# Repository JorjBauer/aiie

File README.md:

# Aiie!

Aiie! is an Apple //e emulator, written ground-up for the Teensy 4.1 (originally for the Teensy 3.6).

The name comes from a game I used to play on the Apple //e back around 1986 - Ali Baba and the Forty Thieves, published by Quality Software in 1981.

[http://crpgaddict.blogspot.com/2013/07/game-103-ali-baba-and-forty-thieves-1981.html](http://crpgaddict.blogspot.com/2013/07/game-103-ali-baba-and-forty-thieves-1981.html)

When characters in the game did damage to each other, they exclaimed something like "HAH! JUST A SCRATCH!" or "AAARGH!" or "OH MA, I THINK ITS MY TIME" [sic]. One of these exclamations was "AIIYEEEEE!!"

## Desktop version

As of 2026, there's a full desktop build of Aiie - but it's not here. Take a look [https://whimology.com/aiie/](on whimology.com) for the full releases.

## Build log:

  [https://hackaday.io/project/19925-aiie-an-embedded-apple-e-emulator](https://hackaday.io/project/19925-aiie-an-embedded-apple-e-emulator)

# Getting the ROMs

As with many emulators, you have to go get the ROMs yourself. I've got the ROMs that I dumped out of my Apple //e. You can probably get yours a lot easier.

There are two files that you'll need:

* apple2e.rom  -- a 32k dump of the entire Apple //e ROM
* disk.rom     -- a 256 byte dump of the DiskII controller ROM (16-sector P5)

The MD5 sums of those files are:

* 003a780b461c96ae3e72861ed0f4d3d9 apple2e.rom
* 2020aa1413ff77fe29353f3ee72dc295 disk.rom
From those, the appropriate headers will be automatically generated by "make roms" (or any other target that relies on the ROMs).

The hard-disk card's ROM (hd32.rom), the mouse card's ROM (mouse.rom) and the parallel printer card's ROM (parallel.rom) are Aiie's own, written for the 65C02 in apple/hd32rom.s, apple/mouserom.s and apple/parallelrom.s. The assembled images are bundled, so nothing has to be downloaded or assembled to build. After changing a source, "make firmware" reassembles them; that needs ca65 and ld65 from the cc65 suite. The printer ROM keeps the Apple card's Control-I commands (I/M reset, K/O toggle the line feed, nH/nL and nJ/nN set the width and stop the screen echo, a control character becomes the new command character) and keeps Applesoft's cursor column in step with the printer so PRINT with commas, TAB( and HTAB line up on paper.

# Building (for the Teensy)

The directory 'teensy' contains 'teensy.ino' - the Arduino development environment project file. You'll need to open that up and compile from within.

However.

I built this on a Mac, and I used a lot of symlinks because of limitations in the Arduino IDE. There's no reason that shouldn't work under Linux, but I have absolutely no idea what Windows will make of it. I would expect trouble. No, I won't accept pull requests that remove the symlinks and replace them with the bare files. Sorry.

Also, you'll have to build the ROM headers (above) with 'make roms' before you can build the Teensy .ino file.

If anyone knows how to make the Arduino development environment do any form of scripting that could be used to generate those headers, I'd gladly adopt that instead of forcing folks to run the Perl script via Makefile. And if you have a better way of dealing with subfolders of code, with the Teensy-specific code segregated as it is, I'm all ears...

I compile this with optimization set to "Faster" for the Teensy 4.1 at 528MHz - I've been successful underclocking it to increase the battery life. YMMV, the Teensy 4.1 will run up to 600MHz.

## Environment and Libraries

I have built this with Arduino 1.8.13 and TeensyDuino 1.54b5 and Arduino 2.3.7 and Teensy 1.59.0.

      https://www.pjrc.com/teensy/td_download.html

These libraries I'm using right from Teensy's environment: TimerOne; SPI; EEPROM; Time; Keypad; SdFat (previously called "SdFat-beta" but renamed in TeensyDuino 1.54).

You'll also need the ILI9341_t3n library from

       https://github.com/KurtE/ILI9341_t3n/

As of this writing, the master branch does not work for Aiie; but the branch "dma_new_fix" is fine. I'd recommend checking out that branch if it exists.

# Running (on the Teensy)

The reset/menu button (F10 on a keyboard) freezes the Apple //e and brings up the BIOS: one panel of settings in the style of the IIgs control panel. Up and Down pick a row, Left and Right change a value, Return opens a row that ends in "...", and Escape goes back (or, from the main list, resumes the //e).

## The main list

* **Resume**: return to the running Apple //e.
* **Reset the //e (warm)**: equivalent to pressing Ctrl-Reset on the real hardware. Hold both joystick buttons before selecting Reset to trigger the Apple //e self-test.
* **Reboot the //e (cold)**: reboot the emulated machine without ejecting disks.
* **Reboot and eject disks**: full power-cycle: ejects all disks and reboots.
* **Disk drive 1 / 2** and **Hard drive 1 / 2**: what is in each drive. Return opens a file browser; pick an image to insert it, or the "Eject" row at the top of the list to remove what is there. Type to narrow the list. Floppies: .dsk, .po, .nib and .woz (.nib images aren't heavily tested for write support). Hard drives: raw 32MB .img/.hdv files, or .2mg.
* **Cards...**, **Display...**, **Paddles...**, **Network...**: screens of their own, below.
* **Volume**: the speaker volume (0 to 15).
* **CPU speed**: Half (511.5 kHz), 1x (1.023 MHz), 2x (2.046 MHz) and 4x (4.092 MHz); the desktop build goes on to 8x, 16x, 128x and 256x.
* **Advanced...**: drop to the Apple //e monitor prompt (useful for debugging); the debug overlay, which cycles through off, FPS, memory free, paddles, PC, cycles, battery, time, disk and network; and the snapshot (see "Suspend and Restore" below). On the Teensy this is also where the firmware is updated from an AIIE.HEX on the SD card.
* **About Aiie**: version and build information.

## Cards

Assigns cards to slots 1 through 7, or 0 to remove a card. Type a digit to put the highlighted card in that slot directly, or step through the slots with Left and Right. If two cards conflict (same slot), the other card is moved to the lowest free slot. Slot 3 only suits the Uthernet, since the //e's own 80-column firmware lives there.

* **Disk II**: default slot 6.
* **Parallel printer**: default slot 1.
* **Hard disk**: default slot 7.
* **Mouse**: off by default; works in any slot but 3.
* **Mockingboard**: default slot 4.
* **Uthernet II**: off by default.
* **RamWorks**: the size of the auxiliary memory expansion, in megabytes, or "not installed".
* **Reset to defaults**: restores the default slot assignments.

Card changes are saved and persist across power cycles. A change cannot take effect in the running machine (the //e's boot scan has already run), so once you change a slot, Resume is disabled until you Reset or Reboot.

## Display

* **Display type**: cycles through four video modes: RGB, NTSC-like, B&W, and Mono.
* **Video7 color text**: whether the machine has an RGB card with the Video7 color-text extensions (see video7.md).
* **Luminance cutoff**: the brightness at which a B&W pixel is lit; Left/Right step it by one, - and + by sixteen.

### Display modes

"Display type" has four values, and they're only really implemented for text and hi-res modes (not for lo-res modes). To describe them, I have to talk about the details of the Apple II display system.

In hires modes, the Apple II can only display certain colors in certain horizontal pixel columns. Because of how the composite video out works, the color "carries over" from one pixel to its neighbor; multiple pixels turned on in a row makes them all white. Which means that, if you're trying to display a picture in hires mode, you get color artifacts on the edges of white areas.

The Apple Color Composite Monitor had a button on it that turned on "Monochrome" mode, with the finer resolution necessary to display the pixels without the color cast. So its two display modes would be the ones I call "NTSC-like" and "Black and White."

There are two other video modes. The "RGB" mode (the default, because it's my preference) shows the color pixels as they're actually drawn in to memory. That means there can't be a solid field of, for example, orange; there can only be vertical stripes of orange with black between them.

The last mode is "Monochrome" which looks like the original "Monitor II", a black-and-green display.

## Paddles

Flips either paddle axis, and plots the live paddle position in a target so you can check them.

## Network

The Uthernet II card's slot, the virtual subnet the NAT hands the Apple, and the inbound ports to forward to it. On the Teensy this is also where the WiFi name and password go, with a Connect row and a live link status; on the desktop the emulator rides the host's own connection, so there is nothing to join, and a port offset lets it open privileged ports without root.

The Teensy uses a ESP-01 for network access. The ESP-01 is limited to 4 active connections - that's a combination of inbound and outbound. If you set 3 different ports for inbound traffic (which are necessary because the Apple might be using raw sockets on the Uthernet, thus we have no way to tell the ESP-01 about its incoming traffic without this configuration) you only have 1 socket available for outbound traffic. If you set four listening ports, you won't be able to connect any outbound sessions at all.

There are a couple problems with the ESP-01 as-wired in the Aiie R9 PCB. I designed the PCB many years before actually wiring up the ESP-01 so it's not surprising that I didn't quite have it right. You'll need to add a 470uF and 0.1uF capacitor (10v) right at the ESP-01's power pins; and 10uF (10v) on the 3.3v regulator output. The device does not like the ESP-01 being turned on after you've booted the Aiie - it doesn't cause damage, but will reboot the machine.

I'm unlikely to build a R10 PCB unless I get specific requests for it. Networking support on an Apple //e emulator is *so* esoteric - nobody's been beating down my door asking for it. But I do have other thoughts of what I might do with the core work from this project, for a new hardware build in future...

## Suspend and Restore

The Teensy can be fully suspended and restored -- including what disks are inserted. It's a full VM hibernation. It currently writes to a file named "suspend.vm" in the root of the MicroSD card. (I would like to be able to select from multiple suspend/restore files eventually. It wouldn't be terribly hard; it's just that the BIOS interface is very limited.)

# Building (on a Mac)

This wasn't the initial purpose of this emulator, but I've built on to it as the first test target for most functionality over the past 9 years. The SDL build works with MacOS 10.11.6 and Homebrew or newer, and you can build and run it like this:

```
  $ make sdl
  $ ./aiie-sdl /path/to/disk.dsk
```

As the name implies, this requires that SDL is installed and in /usr/local/lib. I've done that with Homebrew like this

```
  $ brew install sdl2
```

When running, F10 enters the BIOS.

# Building (on Linux)

Years ago I experimented with Aiie running under a handmade OS on a Raspberry Pi Zero W; the hardware is decent, and cheap. I just don't want Linux in the way. So I built JOSS (see [my Hackaday page about JOSS](https://hackaday.io/project/19925-aiie-an-embedded-apple-e-emulator/log/87286-entry-18-pi-zero-w-and-joss)). 

Well, performance under JOSS is poor, so I built a Linux framebuffer wrapper for Aiie so that I can do performance testing on the Zero W, directly between JOSS and Linux. 

```
$ make linuxfb
$ ./linuxfb
```

There's no guarantee that this will still build; I don't have that environment any longer, and haven't tried to maintain it. I will probably purge it from the master branch in the future and it can live on in the git history.

# Building for the web or electron

You'll find a good number of #ifdefs related to EMSCRIPTEN in the code, but no WASM build here.

In 2026 I've needed a web build of this for a demonstration. Unrelated, I've been building a number of games in Electron for cross-platform support. It's not packaged here - it shares a framework with the games I've written - but the executables are [available on their own site](https://github.com/JorjBauer/aiie-electron-app/) if you want to run this as a standalone application. And stay tuned, I've got a web presence for an upcoming (fall 2026) talk.

# Mockingboard

The original Mockingboard ("Mockingboard A") is fully supported. By default it is installed in Slot 4, but this can be changed (or disabled) from the Cards tab in the BIOS. Both speaker audio and Mockingboard audio are mixed together in the single audio output.

# VM

The virtual machine architecture is broken in half - the virtual and physical pieces. There's the root VM object (vm.h), which ties together the MMU, virtual keyboard, and virtual display.

Then there are the physical interfaces, which aren't as well organized. They exist as globals in globals.cpp:

```
	   FileManager *g_filemanager = NULL;
	   PhysicalDisplay *g_display = NULL;
	   PhysicalKeyboard *g_keyboard = NULL;
	   PhysicalSpeaker *g_speaker = NULL;
	   PhysicalPaddles *g_paddles = NULL;
```

There are the two globals that point to the VM and the virtual CPU:

```
	   Cpu *g_cpu = NULL;
	   VM *g_vm = NULL;
```

And there are two global configuration values that probably belong in
some sort of Prefs class:

```
	   int16_t g_volume;
	   uint8_t g_displayType;
```

# CPU

The CPU is a full and complete 65C02. It supports all of the 65C02 documented and undocumented opcodes:

	   http://www.oxyron.de/html/opcodes02.html

The timing of the CPU is close to, but not quite, correct. It doesn't count cycles due to page boundary crossings during branch instructions, for example. (See the "cycle count footnotes" in cpu.cpp.)

The CPU passes all of the the 6502 tests from here, including the undocumented ADC and SBC handling of Decimal mode and the overflow flag:

    https://github.com/Klaus2m5/6502_65C02_functional_tests

Doing a 

```
$ make test
```

will build the test harness and execute the three tests that encompass all others. (There are more tests in the **tests/** directory - only 3 of them are truly unique.) Two of the tests should emit

    All tests successful!

while the third says

    Test complete. Result: passed

# Caveats

This *requires* TeensyDuino 1.54 beta 5 or later for SdFat long file name support and raw USB keyboard scancode support (see Environment and Libraries above).

Audio runs with its own internal resampler (WSOLA-based) which should keep it sounding reasonable, even if you tell Aiie to run at a different clock speed.

The LinuxFB build is currently unmaintained and definitely broken.

Disk write protection isn't implemented.

If you don't have an SD card inserted when you turn on Aiie, you can't insert one and use it without power cycling. (The card driver is only initialized on hardware startup.)

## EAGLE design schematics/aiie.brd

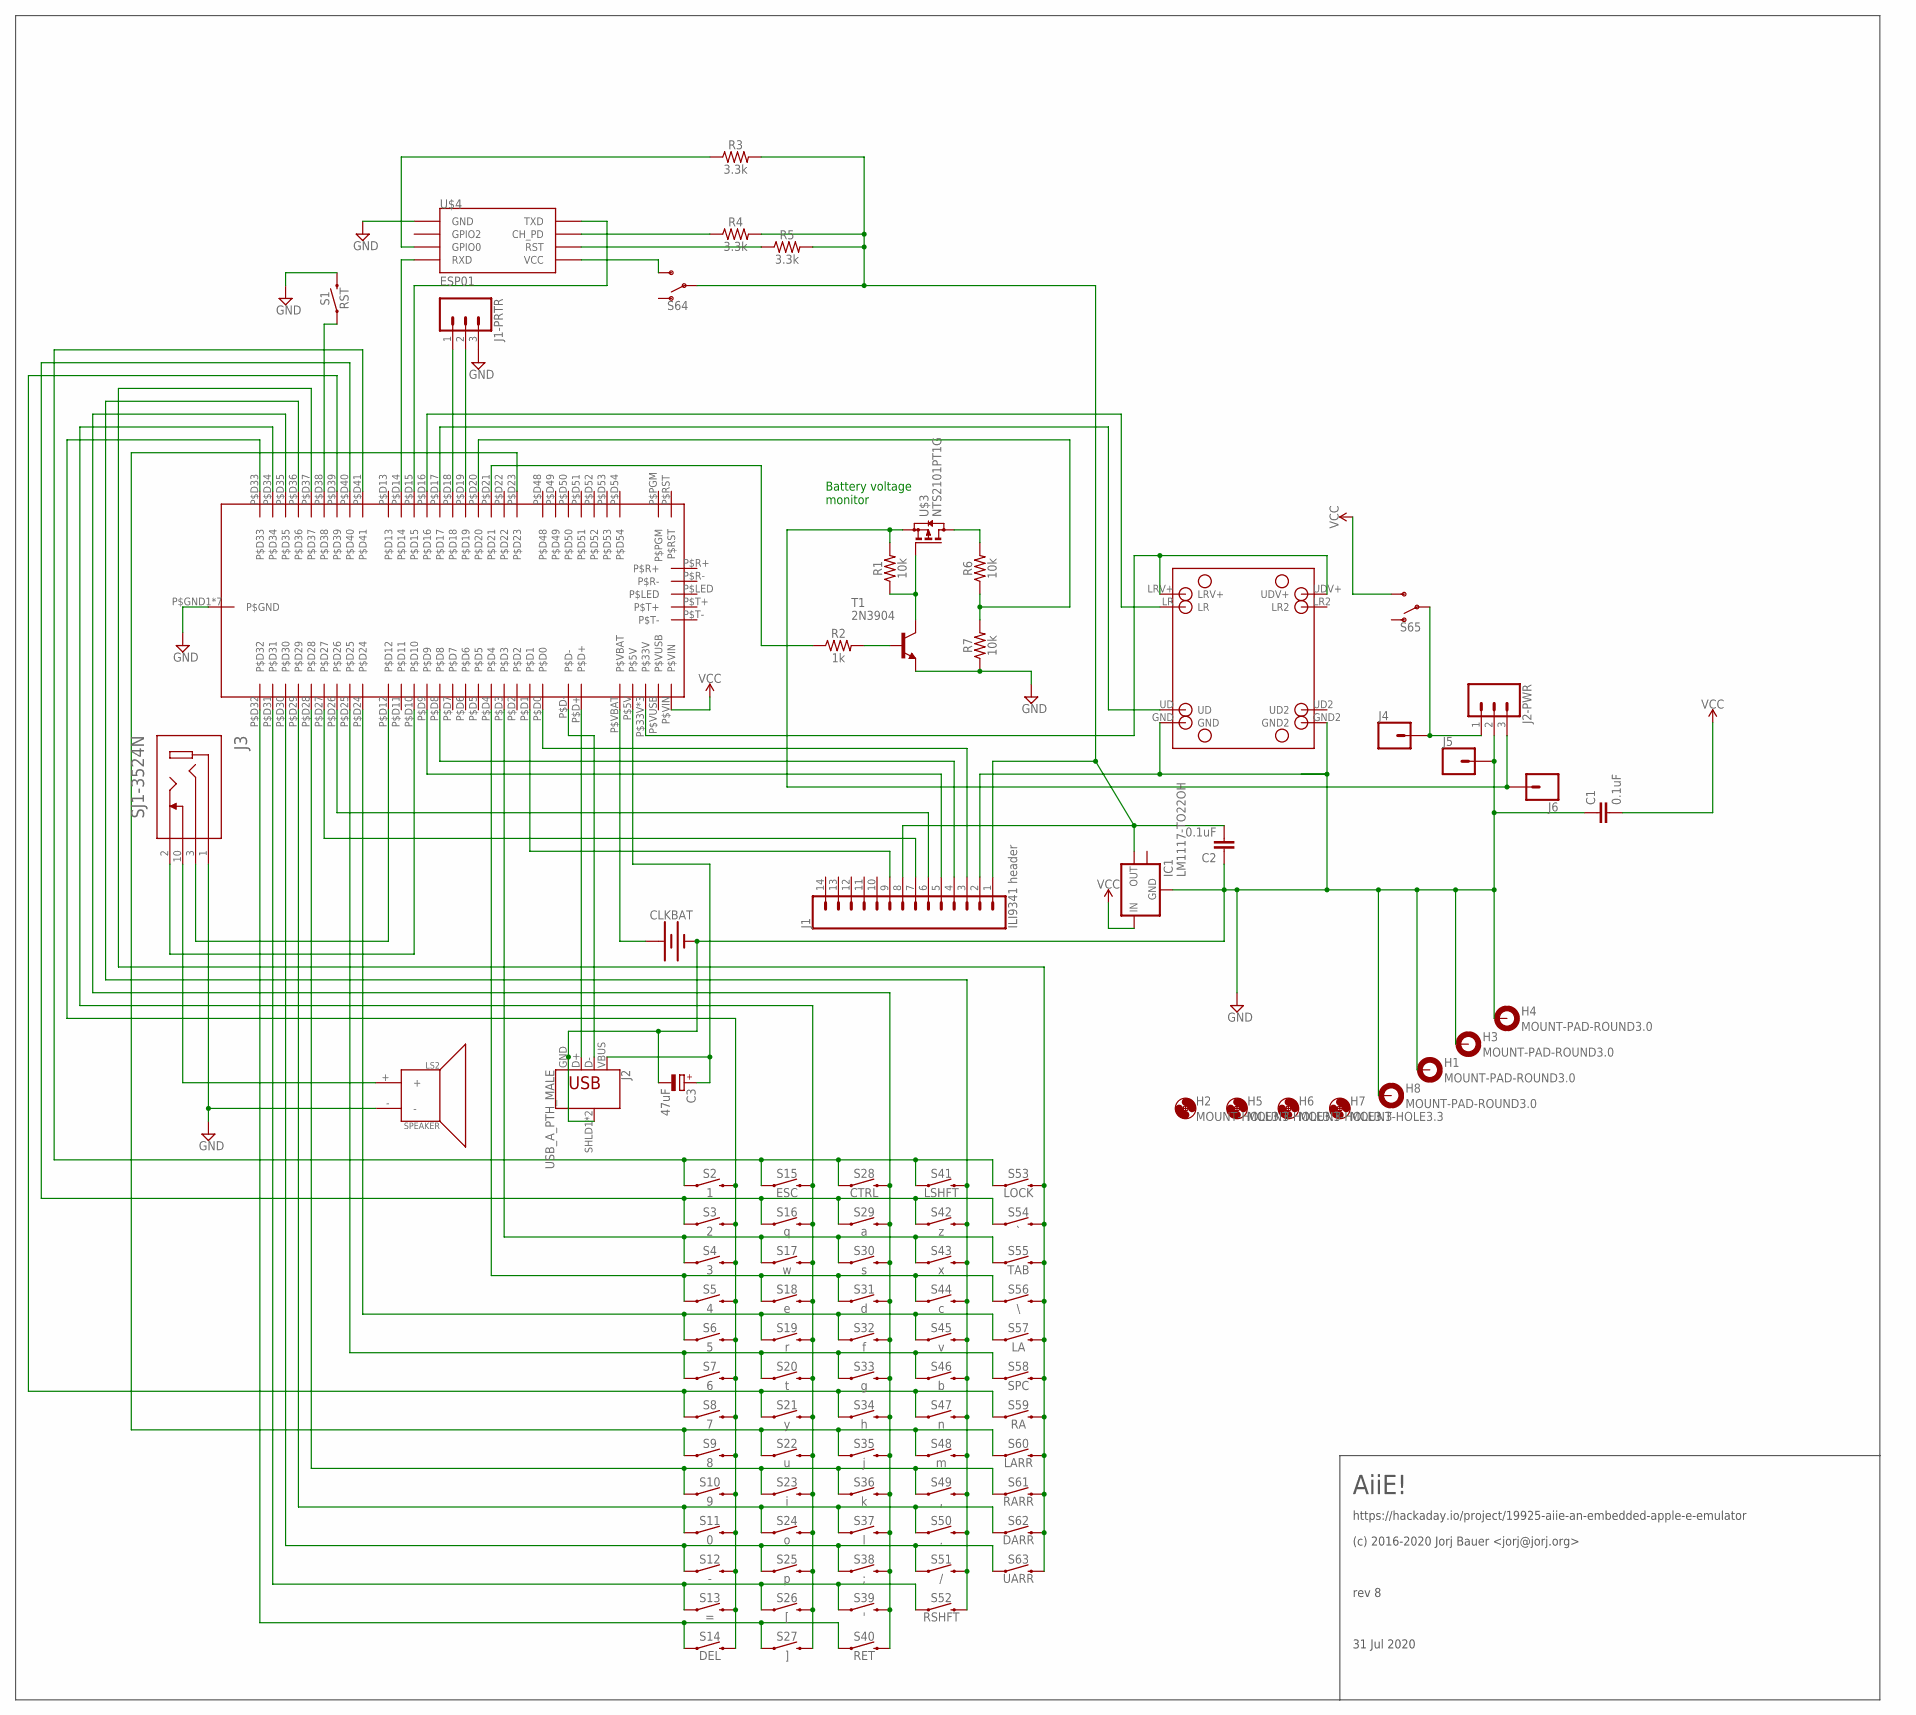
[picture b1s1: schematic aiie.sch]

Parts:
C1, C2: 0.1uF; C025_050-025X075
C3: 47uF; CAPPRD508W65D1000H1100B
CLKBAT: BATTERY-20MM_PTH; BATTCOM_20MM_PTH
H1, H3, H4, H8: MOUNT-PAD-ROUND3.0; 3,0-PAD
H2, H5, H6, H7: MOUNT-HOLE3.3; 3,3
IC1: LM1117-TO22OH; TO220L1
J1: ILI9341 header; 1X14
J1-PRTR, J2-PWR: CONN_03; 1X03
J2: USB_A_PTH_MALE; USB-A-H
J3: SJ1-3524N; CUI_SJ1-3524N
J4, J5, J6: CONN_01; 1X01
LS2: SPEAKER; PCB_MOUNT_SPEAKER
R1, R6, R7: 10k; AXIAL-0.3
R2: 1k; AXIAL-0.3
R3, R4, R5: 3.3k; AXIAL-0.3
S1: RST; TACTILE_SWITCH_PTH_6.0MM
S2: 1; TACTILE_SWITCH_PTH_6.0MM
S3: 2; TACTILE_SWITCH_PTH_6.0MM
S4: 3; TACTILE_SWITCH_PTH_6.0MM
S5: 4; TACTILE_SWITCH_PTH_6.0MM
S6: 5; TACTILE_SWITCH_PTH_6.0MM
S7: 6; TACTILE_SWITCH_PTH_6.0MM
S8: 7; TACTILE_SWITCH_PTH_6.0MM
S9: 8; TACTILE_SWITCH_PTH_6.0MM
S10: 9; TACTILE_SWITCH_PTH_6.0MM
S11: 0; TACTILE_SWITCH_PTH_6.0MM
S12: -; TACTILE_SWITCH_PTH_6.0MM
S13: =; TACTILE_SWITCH_PTH_6.0MM
S14: DEL; TACTILE_SWITCH_PTH_6.0MM
S15: ESC; TACTILE_SWITCH_PTH_6.0MM
S16: q; TACTILE_SWITCH_PTH_6.0MM
S17: w; TACTILE_SWITCH_PTH_6.0MM
S18: e; TACTILE_SWITCH_PTH_6.0MM
S19: r; TACTILE_SWITCH_PTH_6.0MM
S20: t; TACTILE_SWITCH_PTH_6.0MM
S21: y; TACTILE_SWITCH_PTH_6.0MM
S22: u; TACTILE_SWITCH_PTH_6.0MM
S23: i; TACTILE_SWITCH_PTH_6.0MM
S24: o; TACTILE_SWITCH_PTH_6.0MM
S25: p; TACTILE_SWITCH_PTH_6.0MM
S26: [; TACTILE_SWITCH_PTH_6.0MM
S27: ]; TACTILE_SWITCH_PTH_6.0MM
S28: CTRL; TACTILE_SWITCH_PTH_6.0MM
S29: a; TACTILE_SWITCH_PTH_6.0MM
S30: s; TACTILE_SWITCH_PTH_6.0MM
S31: d; TACTILE_SWITCH_PTH_6.0MM
S32: f; TACTILE_SWITCH_PTH_6.0MM
S33: g; TACTILE_SWITCH_PTH_6.0MM
S34: h; TACTILE_SWITCH_PTH_6.0MM
S35: j; TACTILE_SWITCH_PTH_6.0MM
S36: k; TACTILE_SWITCH_PTH_6.0MM
S37: l; TACTILE_SWITCH_PTH_6.0MM
S38: ;; TACTILE_SWITCH_PTH_6.0MM
S39: '; TACTILE_SWITCH_PTH_6.0MM
S40: RET; TACTILE_SWITCH_PTH_6.0MM
S41: LSHFT; TACTILE_SWITCH_PTH_6.0MM
S42: z; TACTILE_SWITCH_PTH_6.0MM
S43: x; TACTILE_SWITCH_PTH_6.0MM
S44: c; TACTILE_SWITCH_PTH_6.0MM
S45: v; TACTILE_SWITCH_PTH_6.0MM
S46: b; TACTILE_SWITCH_PTH_6.0MM
S47: n; TACTILE_SWITCH_PTH_6.0MM
S48: m; TACTILE_SWITCH_PTH_6.0MM
S49: ,; TACTILE_SWITCH_PTH_6.0MM
S50: .; TACTILE_SWITCH_PTH_6.0MM
S51: /; TACTILE_SWITCH_PTH_6.0MM
S52: RSHFT; TACTILE_SWITCH_PTH_6.0MM
S53: LOCK; TACTILE_SWITCH_PTH_6.0MM
S54: `; TACTILE_SWITCH_PTH_6.0MM
S55: TAB; TACTILE_SWITCH_PTH_6.0MM
S56: \\; TACTILE_SWITCH_PTH_6.0MM
S57: LA; TACTILE_SWITCH_PTH_6.0MM
S58: SPC; TACTILE_SWITCH_PTH_6.0MM
S59: RA; TACTILE_SWITCH_PTH_6.0MM
S60: LARR; TACTILE_SWITCH_PTH_6.0MM
S61: RARR; TACTILE_SWITCH_PTH_6.0MM
S62: DARR; TACTILE_SWITCH_PTH_6.0MM
S63: UARR; TACTILE_SWITCH_PTH_6.0MM
S64, S65: SWITCH-SPDT-PTH-11.6X4.0MM; SWITCH_SPDT_PTH_11.6X4.0MM
T1: 2N3904; TO92
U$1: PARALLAX2AXIS
U$2: TEENSY41
U$3: NTS2101PT1G; SOT323
U$4: ESP01

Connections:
GND: C1.1, C2.1, C3.2 (-), CLKBAT.2 (-), H1.B3,0, H3.B3,0, H4.B3,0, H8.B3,0, IC1.1 (GND), J1.2, J1-PRTR.3, J2.GND, J2.SHLD1 (SHIELD), J2.SHLD2 (SHIELD), J2-PWR.2, J3.1, J5.1, LS2.-, R7.P$1 (1), S1.3 (2), T1.3 (E), U$1.GND, U$1.GND2, U$2.P$GND1 (P$GND), U$2.P$GND2 (P$GND), U$2.P$GND3 (P$GND), U$2.P$GND4 (P$GND), U$2.P$GND5 (P$GND), U$2.P$GND6 (P$GND), U$2.P$GND7 (P$GND), U$4.GND
unnamed: CLKBAT.1 (+), U$2.P$VBAT
unnamed: S2.3 (2), S3.3 (2), S4.3 (2), S5.3 (2), S6.3 (2), S7.3 (2), S8.3 (2), S9.3 (2), S10.3 (2), S11.3 (2), S12.3 (2), S13.3 (2), S14.3 (2), U$2.P$D33
unnamed: S15.3 (2), S16.3 (2), S17.3 (2), S18.3 (2), S19.3 (2), S20.3 (2), S21.3 (2), S22.3 (2), S23.3 (2), S24.3 (2), S25.3 (2), S26.3 (2), S27.3 (2), U$2.P$D34
unnamed: S28.3 (2), S29.3 (2), S30.3 (2), S31.3 (2), S32.3 (2), S33.3 (2), S34.3 (2), S35.3 (2), S36.3 (2), S37.3 (2), S38.3 (2), S39.3 (2), S40.3 (2), U$2.P$D35
unnamed: S41.3 (2), S42.3 (2), S43.3 (2), S44.3 (2), S45.3 (2), S46.3 (2), S47.3 (2), S48.3 (2), S49.3 (2), S50.3 (2), S51.3 (2), S52.3 (2), U$2.P$D36
unnamed: S53.3 (2), S54.3 (2), S55.3 (2), S56.3 (2), S57.3 (2), S58.3 (2), S59.3 (2), S60.3 (2), S61.3 (2), S62.3 (2), S63.3 (2), U$2.P$D37
unnamed: S2.1, S15.1, S28.1, S41.1, S53.1, U$2.P$D41
unnamed: S4.1, S17.1, S30.1, S43.1, S55.1, U$2.P$D3
unnamed: S3.1, S16.1, S29.1, S42.1, S54.1, U$2.P$D40
unnamed: S1.1, U$2.P$D38
unnamed: S5.1, S18.1, S31.1, S44.1, S56.1, U$2.P$D4
unnamed: J2.D-, U$2.P$D-
unnamed: S6.1, S19.1, S32.1, S45.1, S57.1, U$2.P$D24
unnamed: C2.2, IC1.2 (VOUT), J1.1, J1.8, R3.P$2 (2), R4.P$2 (2), R5.P$2 (2), S64.2
unnamed: S7.1, S20.1, S33.1, S46.1, S58.1, U$2.P$D25
unnamed: J1.3, U$2.P$D0
unnamed: S8.1, S21.1, S34.1, S47.1, S59.1, U$2.P$D39
unnamed: J1.4, U$2.P$D8
unnamed: S9.1, S22.1, S35.1, S48.1, S60.1, U$2.P$D23
unnamed: J1.5, U$2.P$D9
unnamed: S10.1, S23.1, S36.1, S49.1, S61.1, U$2.P$D28
unnamed: J1.6, U$2.P$D26
unnamed: S11.1, S24.1, S37.1, S50.1, S62.1, U$2.P$D29
unnamed: J1.7, U$2.P$D27
unnamed: S12.1, S25.1, S38.1, S51.1, S63.1, U$2.P$D30
unnamed: S13.1, S26.1, S39.1, S52.1, U$2.P$D31
unnamed: S14.1, S27.1, S40.1, U$2.P$D32
unnamed: J1.9, U$2.P$D1
unnamed: U$1.UD, U$2.P$D17
unnamed: J2.D+, U$2.P$D+
unnamed: J3.2, U$2.P$D10
unnamed: S64.3 (S), U$4.VCC
unnamed: J3.3, U$2.P$D12
unnamed: R3.P$1 (1), U$4.GPIO0
unnamed: R4.P$1 (1), U$4.CH_PD
unnamed: R5.P$1 (1), U$4.RST
unnamed: U$2.P$D14, U$4.RX (RXD)
unnamed: U$2.P$D15, U$4.TX (TXD)
unnamed: J3.10, LS2.+
unnamed: J2-PWR.3, J6.1, R1.P$2 (2), U$3.2 (S)
unnamed: R1.P$1 (1), T1.1 (C), U$3.1 (G)
unnamed: U$1.LR, U$2.P$D16
unnamed: J1-PRTR.1, U$2.P$D18
unnamed: J1-PRTR.2, U$2.P$D19
unnamed: R2.P$2 (2), T1.2 (B)
unnamed: J2-PWR.1, J4.1, S65.2
unnamed: U$1.LRV+, U$1.UDV+, U$2.P$33V, U$2.P$33V2 (P$33V), U$2.P$33V3 (P$33V)
unnamed: R6.P$1 (1), R7.P$2 (2), U$2.P$D20
unnamed: R6.P$2 (2), U$3.3 (D)
unnamed: R2.P$1 (1), U$2.P$D21
unnamed: C3.1 (+), J2.VBUS, U$2.P$5V
VCC: C1.2, IC1.3 (VIN), S65.3 (S), U$2.P$VIN

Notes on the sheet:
AiiE!
https://hackaday.io/project/19925-aiie-an-embedded-apple-e-emulator
(c) 2016-2020 Jorj Bauer <jorj@jorj.org>
rev 8
31 Jul 2020
Battery voltage monitor

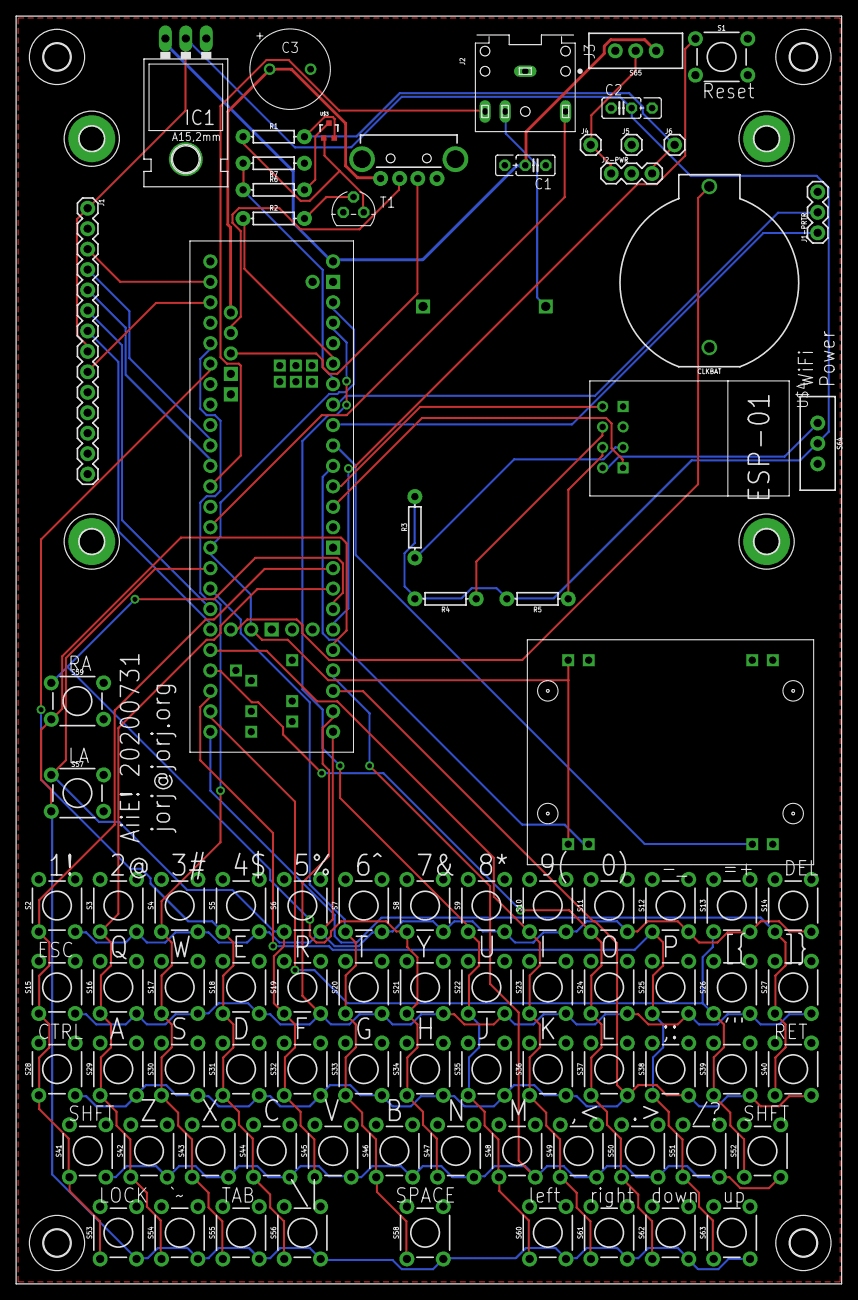
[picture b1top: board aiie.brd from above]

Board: 2 copper layers, 102.5 x 157.5 mm, 99 parts (1 on the bottom side), 53 nets.

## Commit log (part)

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2018-02-07 show that suspend/resume are happening
2018-02-07 fix broken constants kn linuxfb keyboard driver
2018-02-07 added basic About menu
2018-02-07 abstracting directory filename filter
2018-02-07 SDL quiescent audio level = 0x80, not 0x00
2018-02-07 finish abstracting file extension filter
2018-02-17 No-Slot clock conversion
2018-02-17 Include no-slot clock in Teensy build
2018-02-19 remove unused SDL_Mutex
2018-02-19 default to "Emphasized" text mode (easier to read)
2018-02-19 disable CPU debugging
2018-06-16 test abstraction
2018-06-16 CPU fixes - notably ADC/SBC in Decimal mode with invalid BCD values
2018-06-16 fix return result on success of decimal tests
2018-06-16 updated for full 65c02 and linuxfb
2019-02-13 extended SDL debugger
2019-02-13 added script to side-load a binary right in to a running SDL build via the debugger
2019-02-20 first working Woz code (read-only, and only non-copyprotected disks)
2019-02-20 Real-time dropout only makes sense on the Teensy; don't force it on SDL
2019-02-20 rebuilt SDL speaker driver
2019-02-21 incremental cleanup and prep for dynamic track loading (instead of full track preloading)
2019-02-21 dynamically read track data
2019-02-21 update Teensy build to include Woz
2019-02-22 fixed bit length of tracks; added actual random fake bits. Passes most test Woz images now.
2019-02-22 tie disk spin-down to CPU cycles
2020-06-27 incremental improvement for woz disk support
2020-06-28 fixup for using both drives; repair spindown delay (which was a factor of 1000 too aggressive, which is why disk access was slow)
2020-06-28 dynamically load based on reading bits
2020-06-28 fix serialization of diskii object; allow teensy to build w/o caching entire disk images
2020-06-28 simple write support; added teensy abstraction
2020-06-28 add lazy flushing
2020-06-28 add missing abstraction headers
2020-06-28 first pass of compatability functions
2020-06-28 bring inline with outer filesystem changes
2020-06-28 remove obsolete filemanager methods
2020-06-28 basic improvement
2020-06-30 when disk is spinning and other disk is selected, make sure the newly selected disk starts spinning
2020-07-01 revert to reset-on-intr
2020-07-01 fixes for disk writing and rotational speed
2020-07-03 allow woz images
2020-07-03 prefs should use MAXPATH
2020-07-03 update comments about RAM page handling
2020-07-03 fix crasher when accessing empty drive
2020-07-03 volatile
2020-07-03 mutex locking support
2020-07-03 temporarily turning off printer for teensy
2020-07-04 better typecasting
2020-07-04 comment out unused code
2020-07-04 add disk track to debugging
2020-07-04 use a common serial abstraction
2020-07-04 bios can select disk debugging
2020-07-04 common serial; added disk debugging
2020-07-04 common serial; disk debugging
2020-07-04 added mutexes
2020-07-04 testing single track cache
2020-07-04 add serialize/deserialize for hd32
2020-07-04 add read and step out
2020-07-04 deserialization fixes
2020-07-04 Revert "testing threads"
    This reverts commit f5b7f19ebba07607807a8dabed0c78e5c13364f7.
2020-07-04 removing debugging
2020-07-05 re-enable printer for Teensy
2020-07-06 first pass at Teensy 4.1 support
2020-07-06 conversion to 16-bit blit
2020-07-06 fix typecast on serialize
2020-07-07 bump clock back to 65
2020-07-07 testing USB host
2020-07-08 *nix filesystem fixes
2020-07-08 block read fix; off-by-one read fix when reading single bytes
2020-07-08 working on USB keyboard support; fix pin assignments
2020-07-08 bump up drawing clock speed
2020-07-08 threads conversion
2020-07-08 turn off serial debugging
2020-07-08 fix bios drawing
2020-07-08 fix SDL build
2020-07-09 working on 80-column text rendering
2020-07-09 remove obsolete display/sound priority option
2020-07-09 moving around a few pins
2020-07-10 working on speaker conversion
2020-07-10 Fix *nix build deps
2020-07-10 better (simpler, more modern) dependency handling
2020-07-10 add clarifying comment
2020-07-11 better caching when reading directories
2020-07-11 sort disk images in the BIOS
2020-07-12 reworking thread timing
2020-07-12 Testing running inline instead of in threads
2020-07-12 properly draw UI on startup
2020-07-12 debugging
2020-07-12 common debugging buffer (fix some memory overruns); consistent timing improvements
2020-07-13 removed threads; bones for audio in place
2020-07-13 Audio improvements
2020-07-14 account for missing cycles auto-filled when speaker is quiescent
2020-07-14 cleanup
2020-07-15 speaker fixes; committed to removing threads
2020-07-15 convert to ili9341_t3n library to use full DMA transfers
2020-07-15 fix chirp on startup
2020-07-15 convert to MQS (move keyboard and display to suit)
2020-07-31 layout fixes: remove unnecessary USB cap (it's on the teensy); fix usb part; ensure parallel D+/D- USB traces
2020-07-31 fixed v9
2020-08-02 get actual return value from ::write()
2020-08-02 convert cpu cycle counter to int64_t
2020-08-02 audio fixes and normalization between hardware types
2020-08-02 fix format
2020-08-03 removed unnecessary includes
2020-08-03 convert to SdFat-beta for long filename support (but conflicts with Audio.h, sadly)
2020-08-03 documented the depth of the latest hack
2020-08-03 fix bounds overflow when drawing characters
2020-08-03 remove macros for threading compatability
2020-12-28 update Teensy to use the new common BIOS
2020-12-28 finish implementing disk and hard disk insertion
2020-12-28 avoid fast-forwarding the CPU after exiting the BIOS
2020-12-28 normalizing SDL BIOS behavior against Teensy
2020-12-29 add battery status
2020-12-29 update to TeensyDuino 1.54b5 for raw USB keypress support
2020-12-29 basic USB keyboard functionality
2020-12-29 fix usb scancode error
2020-12-29 add volume in the SDL build
2020-12-29 fix drawing of volume bar - needs to use the scaled method
2020-12-29 importing old mouse work to new teensy 4.1
2021-01-09 more normalization and commenting
2021-01-09 expand reboot options (and make them understandable)
2021-01-09 initialize cpu speed state in the bios menu so it shows the correct value
2021-01-09 fixups for teensy display
2021-01-09 cleanups for file selection
2021-01-09 fix disk behavior on bios reboot
2021-01-10 fix suspend/resume
2021-01-10 debugging fixes
2021-01-10 remove single cached track hack; convert to EXTMEM on the Teensy 4
2021-01-10 VBL interrupts work; roughing in physical mouse
2021-01-11 rebuild ROM image cleanly
2021-01-11 remove debugging hack
2021-01-11 remove debugging printf
2021-01-11 when writing to ram, use the MMU. Also cleaned up comments.
2021-01-11 adding missing serialization include
2021-01-11 wired in mouse support; left-apple is the mouse button on the teensy for now
2021-01-11 only re-read joystick for mouse posn while mouse is enabled; added comments in mouse rom
2021-01-11 remove dead code
2021-01-11 working on blazing paddles mouse support
2021-01-11 fix for returning from BIOS hanging
2021-01-12 remove incorrect placeholder from before interrupts were in place
2021-01-13 reset time flags when resuming
2021-01-13 more features
2021-01-14 minor improvements and bugfixes in debugging
2021-01-14 added missing addressing modes
2021-01-14 trying to improve resume after debug
2021-01-16 fix transcription error in mouse rom; update irq semantics
2021-01-17 graphics/text page reads don't come from alt banks of RAM
2021-01-18 remove b&w from sdl layer
2021-01-18 fix drawing of single-HGR
2021-01-18 fix missing symlink for teensy mouse
2021-01-19 allow hard drive images with extension "hdv"
2021-01-19 normalize with a 32-bit backing video store, matching the way we use dmaMem in the teensy build
2021-01-19 merging display paths between SDL and Teensy
2021-01-19 add luminance cutoff for B&W mode
2021-01-20 bugfix for usb keyboard auto-repeat
2021-01-20 silence a warning
2021-01-20 remove some of the modules not in use
2021-01-20 startup order fixes; move key-down-map to extmem
2021-01-20 move buffers to extmem
2021-01-20 second HD needs to allow hdv; add missing entry terminators
2021-01-20 workaround for bug in Keypad library: need to set the pull-ups earlier, so the first reading isn't bad
2021-01-21 refreshing so fast was causing crosstalk on the keypad pins and phantom keystrokes. Slowed.
2021-01-21 revert debounce time
2021-01-21 add ILI library doc
2021-01-21 only allow left/right on the root menus
2021-01-21 remove constructs assuming the Y resolution < 256 pixels
2021-01-21 improving the paddle bios config
2021-01-22 remove single-track operation
2021-01-22 abstracting aiie-specific changes to WozSerializer
2021-01-23 remove erroneous offset
2021-01-23 import upstream woz code
2021-01-23 fixes for the SDL build
2021-12-11 documentation updates for 2021
2021-12-12 normalize keypress tracking
2021-12-13 Saving people a step - no need to recompile the mouse rom from apple/mouserom.asm
2022-01-07 reduce flush delay to 3 seconds
2022-01-07 fix autorepeat problem for modifiers
2022-01-07 add SEEK_END
2022-01-07 add flush method
2022-01-07 intergrated latest woz code (serialization disabled)
2022-01-07 minor updates to bill of materials
2022-01-09 update for latest woz model
2022-01-10 latest from wozzle
2022-01-10 building an in-VM test of disk ii workings
2022-01-15 work on the test
2022-01-16 new images for platinum feel
2022-01-18 building local driver
2022-01-18 _cs, not _rst
2022-01-18 working on initialization
2022-01-18 fix duplicated conflicting offset; set up panel as 8-bit; slow down bus while building
2022-01-18 16to-8bpp
2022-01-19 working on DMA transfers
2022-01-20 draws sync
2022-01-20 with working DMA transfers
2022-01-20 everything goes through DMA
2022-01-21 playing with PLL, pixel clock, and SPI bus speed: up to 17 fps
2022-01-21 more DMA framebuffer updates
2022-01-22 fix S_MIXED drawing to prevent full DMA from flashing
2022-01-22 fix constant abstractions
2022-01-22 fix debug message placement
2022-01-22 some DMA cleanup
2022-01-23 more DMA cleanup
2022-01-23 fix status register clear
2022-01-26 abstracting displays
2022-01-30 looking for a bug...
2022-01-30 embed images in 16bpp instead of 24bpp
2022-01-30 fix sdl build to use 16-bit builtins; fix base 8875 image
2022-02-02 dma working again w/ dynamic objects
2022-02-02 default to ILI display
2022-02-02 fix off-by-one when drawing 80 column text
2022-02-02 working on drive activity
2022-02-02 fix drive latches on 9341
2022-02-02 fix text drawing
2022-02-02 fix drive indicators on startup; fix overlay for 9341
2022-02-02 fix for text drawing being clipped... sort of
2022-02-02 fix screen fill on the 8875
2022-02-02 fix overlay for ra8875
2022-02-10 working on blending; fixed SDL drive indicator and bios text drawing
2022-02-10 allow HSV color blending
2022-02-10 add HSV pixel blending for the ILI display in double-hi-res modes
2022-02-10 utility to generate blended pixel values
2026-04-24 fix LSS disk latching
2026-04-24 bump woz: 13-sector support
2026-04-24 More disk latch bit fixups - stale data issues with C08C and C08D, readWriteLatch proper handling, etc.
2026-04-24 woz version bump from wozzle. Fixes for LSS, which fix a bunch of .woz copy-protection reads
2026-04-24 adding read/write tests
2026-04-24 write fixes
2026-04-24 fake bit improvement
2026-04-24 cross-track head parking fix
2026-04-24 WSOLA to scale audio during playback to maintain pitch
2026-04-25 better speaker handling; updated teensy build to work with current libraries
2026-04-25 code cleanup and modernization
2026-04-25 initial draft of mockingboard support - mouse moved to slot 2, mockingboard in 4
2026-04-25 SDL window handling QoL fixes; mockingboard detected in ACS properly, and reset on machine reset
2026-04-25 allow slot changes
2026-04-25 update file cache size
2026-04-25 suspend/restore fix
2026-04-25 audio fixes
2026-04-25 working on sound
2026-04-25 bump about info
2026-04-25 fx-80 updates / rewiring
2026-04-25 fx-80/printing improvements
2026-06-26 woz bugfix for writes falling out of bit-sync
2026-06-26 SDL speaker underflow?
2026-06-28 debugger adds 'T' to dump text screens; added fake baseline noise to keep SDL audio channel active
2026-06-28 wrapper to use the SDL debugger
2026-06-29 add a teensy Makefile target

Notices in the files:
parts and their libraries:
SparkFun-Switches: Licensing: Creative Commons ShareAlike 4.0 International - https://creativecommons.org/licenses/by-sa/4.0
